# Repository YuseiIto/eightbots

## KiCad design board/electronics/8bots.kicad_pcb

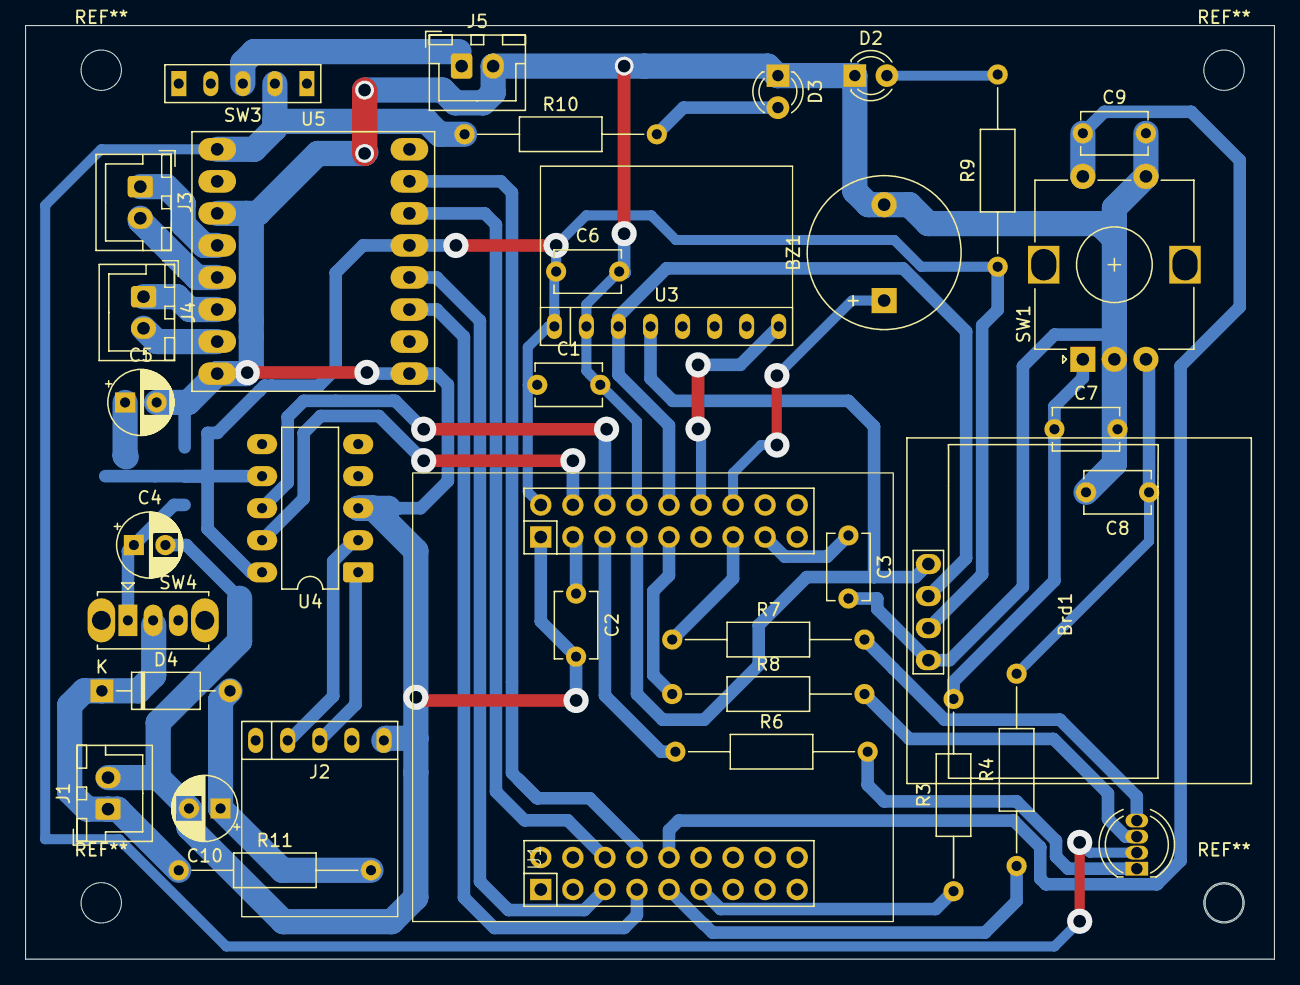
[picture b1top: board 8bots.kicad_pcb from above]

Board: 2 copper layers, 99.0 x 74.0 mm, 37 parts (1 on the bottom side), 38 nets.

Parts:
BZ1: Buzzer; Buzzer_12x9.5RM7.6
Brd1: SSD1306; 128x64OLED
C1, C2, C3, C6, C7, C8, C9: 0.1uF; C_Disc_D5.1mm_W3.2mm_P5.00mm
C4: 10uF; CP_Radial_D5.0mm_P2.50mm
C5: 22uF; CP_Radial_D5.0mm_P2.50mm
C10: 100uF; CP_Radial_D5.0mm_P2.50mm
D1: LED_RABG; LED_D5.0mm-4_RGB
D2, D3: LED; LED_D3.0mm
D4: D; D_A-405_P10.16mm_Horizontal
J1: 9V IN; JST_XH_B2B-XH-A_1x02_P2.50mm_Vertical
J2: USB_B_Micro; MicroUSBBoard
J3: Motor R; JST_XH_B2B-XH-A_1x02_P2.50mm_Vertical
J4: Motor L; JST_XH_B2B-XH-A_1x02_P2.50mm_Vertical
J5: Motor BAT; JST_XH_B2B-XH-A_1x02_P2.50mm_Vertical
R3, R4, R9, R10, R11: 10k; R_Axial_DIN0207_L6.3mm_D2.5mm_P15.24mm_Horizontal
R6, R7, R8: 1k; R_Axial_DIN0207_L6.3mm_D2.5mm_P15.24mm_Horizontal
SW1: RotaryEncoder_Switch; RotaryEncoder_Alps_EC12E-Switch_Vertical_H20mm
SW3: SW_SPDT; SPDT_With_Mounting_Hole
SW4: SW_SPDT; SW_Slide_SPDT_Straight_CK_OS102011MS2Q
U1: ESP32-WROOM-32; ESP-32SBoard
U2: AZ1084-3.3; TO-252-3_TabPin2
U3: GY-521; GY-521_Part_side_up
U4: CH340E; DIP-10_W7.62mm_LongPads
U5: DRV8833 Module; DRV8833_Module

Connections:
+3V3: Brd1.2 (VCC), C1.1, C5.1, C6.1, R9.1, U1.2 (VDD), U2.2 (VO), U3.1 (VCC), U4.7 (VCC), U4.10 (V3), U5.13 (STBY)
/AIN1: U1.8 (IO32), U5.14 (AIN1)
/AIN2: U1.10 (IO25), U5.15 (AIN2)
/BIN1: U1.9 (IO33), U5.12 (BIN1)
/BIN2: U1.11 (IO26), U5.11 (BIN2)
/BUZZER: BZ1.1 (+), U1.28 (IO17)
/EN: C2.1, U1.3 (EN)
/IO0: C3.1, U1.25 (IO0)
/LED_B: R8.1, U1.31 (IO19)
/LED_G: R7.1, U1.27 (IO16)
/LED_R: R6.1, U1.37 (IO23)
/MPU_INT: U1.30 (IO18), U3.8 (INT)
/ROT_A: R3.1, U1.16 (IO13)
/ROT_B: R4.1, U1.13 (IO14)
/ROT_SW: C9.1, SW1.S1, U1.12 (IO27)
/RX0: U1.34 (RXD0/IO3), U4.8 (TXD)
/SCL: Brd1.3 (SCL), U1.33 (IO21), U3.3 (SCL)
/SDA: Brd1.4 (SDA), U1.36 (IO22), U3.4 (SDA)
/TX0: U1.35 (TXD0/IO1), U4.9 (RXD)
/VBAT: D1.2 (A), R10.1, SW3.3 (C), U5.1 (VM)
GND: BZ1.2 (-), Brd1.1 (GND), C1.2, C2.2, C3.2, C4.2, C5.2, C6.2, C7.2, C8.2, C9.2, C10.2, D2.1 (K), D3.1 (K), J1.2, J2.5 (GND), J5.2, SW1.C, SW1.S2, U1.1 (GND), U1.15 (GND), U2.1 (GND), U3.2 (GND), U4.3 (GND), U5.3 (GND), U5.8 (GND), U5.9 (GND)
unnamed: C7.1, R3.2, SW1.A
unnamed: C8.1, R4.2, SW1.B
unnamed: D1.3 (BK), R8.2
unnamed: D1.4 (GK), R7.2
unnamed: D1.1 (RK), R6.2
unnamed: D2.2 (A), R9.2
unnamed: D3.2 (A), R10.2
unnamed: C10.1, D4.2 (A), R11.2
unnamed: D4.1 (K), J1.1, R11.1, SW4.2 (B)
unnamed: J2.3 (D+), U4.1 (UD+)
unnamed: J2.2 (D-), U4.2 (UD-)
unnamed: J3.1, U5.4 (AO1)
unnamed: J3.2, U5.5 (AO2)
unnamed: J4.1, U5.6 (BO2)
unnamed: J4.2, U5.7 (BO1)
unnamed: J5.1, SW3.2 (B)
unnamed: C4.1, SW4.1 (A), U2.3 (VI)

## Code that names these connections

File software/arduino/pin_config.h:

/**
 * pin configuration
 */
#ifndef PIN_CONFIG_H
#define PIN_CONFIG_H

const int PIN_TX0 = 1;
const int PIN_RX0 = 3;

const int PIN_ROT_A = 13;
const int PIN_ROT_B = 14;
const int PIN_ROT_SW = 27;

const int PIN_LED_R = 23;
const int PIN_LED_G = 16;
const int PIN_LED_B = 19;

const int PIN_BUZZER = 17;

const int PIN_MPU_INT = 18;
const int PIN_SDA = 22;
const int PIN_SCL = 21;

const int PIN_MOTOR_AIN1 = 32;
const int PIN_MOTOR_AIN2 = 25;
const int PIN_MOTOR_BIN1 = 33;
const int PIN_MOTOR_BIN2 = 26;

#endif

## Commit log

2021-12-04 Build initial utility
2021-12-04 Basic BFS
2024-08-31 Add renovate.json
2025-03-06 feat: generate_fuzzy_board
2025-03-06 fix: cleanup
2025-03-06 add: electronics
2025-03-06 feat: initiate arduino source code
2025-03-06 chore(.gitignore): update gitignore
2025-03-06 feat: led feature
2025-03-06 feat: Initiate OLED feature
2025-03-06 fix: update fqbn
2025-03-07 feat: Initiate rotary encoder feature
2025-03-07 chore(Makefile): `EraseFlash=all` to ensure the image dump is consistent
2025-03-07 fix: move main sketch from arduino to `arduino/eightbots`
2025-03-07 feat: WIFI_SSID, WIFI_PASSWORDシンボルを定義
2025-03-07 chore(Makefile): Use `arduino-cli board list` for `make set-port`
    To detect network port
2025-03-07 feat: Enable arduino OTA
2025-03-07 feat: beep when connected to WiFi
2025-03-08 feat: initiate motor feature
2025-03-09 feat: configure display text
2025-03-09 refactor: change the configuration order
2025-03-09 fix: change the I2C frequency
2025-03-09 feat: initiate MPU6050 feature
2025-03-09 feat: Configure PWM resolution explicitly
2025-03-09 feat: Configure PWM frequencyt explicitly
2025-03-09 feat: proportional front-facing control
2025-03-09 feat: PID front-facing control
2025-03-10 fix: flip motor direction
2025-03-10 feat: move forward when button pressed
2025-03-11 doc(LICENSES): add license information of `PID` library
